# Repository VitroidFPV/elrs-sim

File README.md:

# ELRS Sim Receiver
Hardware for https://github.com/mikeneiderhauser/CRSFJoystick

> [!CAUTION]
> This hardware is untested and still awaiting ELRS target approval!
> Use/reference at own risk.

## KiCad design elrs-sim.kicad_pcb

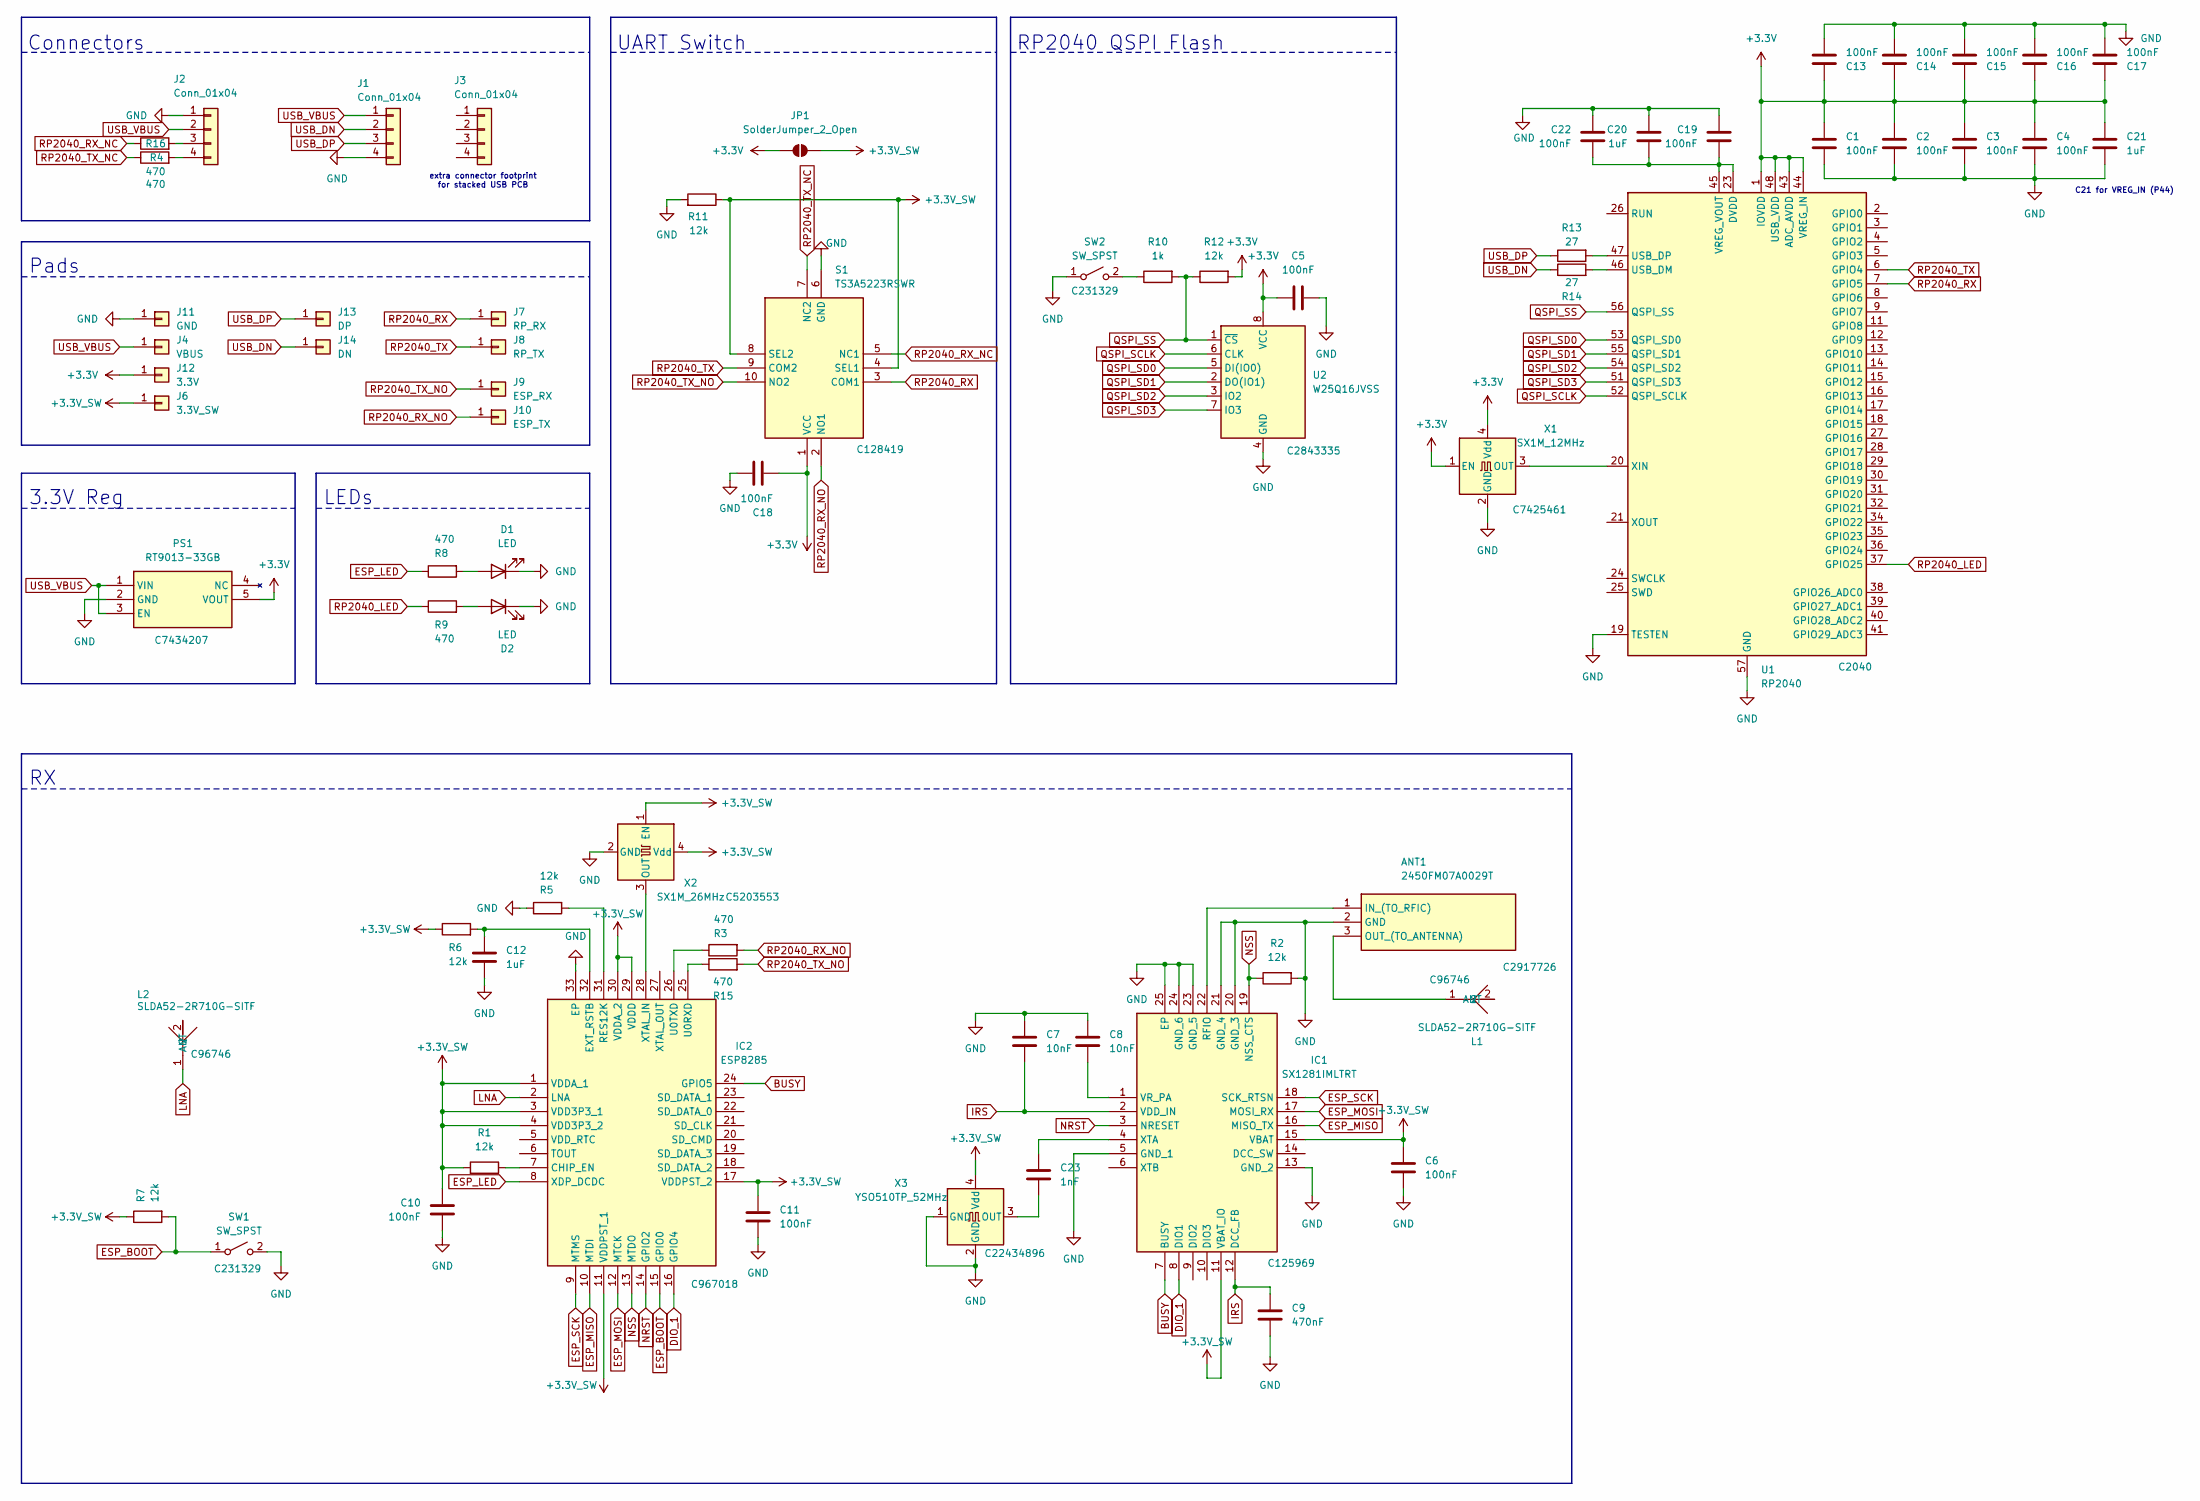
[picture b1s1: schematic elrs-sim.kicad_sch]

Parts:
ANT1: 2450FM07A0029T; Manufacturer_Part_Number 2450FM07A0029T; Mouser Part Number 609-2450FM07A0029T
C1, C2, C3, C4, C5, C6, C10, C11, C13, C14, C15, C16, C17, C18, C19, C22: 100nF; C_0402_1005Metric; LCSC C110251
C7, C8: 10nF; C_0402_1005Metric; LCSC C60133
C9: 470nF; C_0402_1005Metric; LCSC C47339
C12: 1uF; C_0402_1005Metric; LCSC C110251
C20, C21: 1uF; C_0402_1005Metric; LCSC C14445
C23: 1nF; C_0402_1005Metric; LCSC C1523
D1: LED; LED_0603_1608Metric; LCSC C84266
D2: LED; LED_0603_1608Metric; LCSC C84267
IC1: SX1281IMLTRT; QFN50P400X400X100-25N-D; Manufacturer_Part_Number SX1280IMLTRT; Mouser Part Number 947-SX1280IMLTRT
IC2: ESP8285; QFN50P500X500X90-33N-D; Manufacturer_Part_Number ESP8285; Mouser Part Number 356-ESP8285
J1: Conn_01x04; PCB_USB_connector
J2: Conn_01x04; PinHeader_1x04_P2.54mm_Vertical
J3: Conn_01x04; PCB_USB_connector_top
J4: VBUS; PAD_1.5x1.5mm_NO_HOLE
J6: 3.3V_SW; PAD_1.5x1.5mm_NO_HOLE
J7: RP_RX; PAD_1.5x1.5mm_NO_HOLE
J8: RP_TX; PAD_1.5x1.5mm_NO_HOLE
J9: ESP_RX; PAD_1.5x1.5mm_NO_HOLE
J10: ESP_TX; PAD_1.5x1.5mm_NO_HOLE
J11: GND; PAD_1.5x1.5mm_NO_HOLE
J12: 3.3V; PAD_1.5x1.5mm_NO_HOLE
J13: DP; PAD_1.5x1.5mm_NO_HOLE
J14: DN; PAD_1.5x1.5mm_NO_HOLE
JP1: SolderJumper_2_Open; SolderJumper-2_P1.3mm_Open_TrianglePad1.0x1.5mm
L1, L2: SLDA52-2R710G-SITF; ANT-SMD_L5.2-W2.1; LCSC Part C96746
PS1: RT9013-33GB; SOT-23-5; Manufacturer_Part_Number RT9013-33GB; LCSC C7434207
R1, R2, R5, R6, R7, R11, R12: 12k; R_0402_1005Metric; LCSC C22790
R3, R4, R8, R9, R15, R16: 470; R_0402_1005Metric; LCSC C25117
R10: 1k; R_0402_1005Metric; LCSC C11702
R13, R14: 27; R_0402_1005Metric; LCSC C25100
S1: TS3A5223RSWR; UQFN-10_1.3x1.8mm_P0.4mm; Manufacturer_Part_Number TS3A5223RSWR; Mouser Part Number 595-TS3A5223RSWR
SW1, SW2: SW_SPST; SW_SPST_B3U-1000P; LCSC C231329
U1: RP2040; QFN-56-1EP_7x7mm_P0.4mm_EP3.2x3.2mm; LCSC C2040
U2: W25Q16JVSS; Winbond_USON-8-1EP_3x2mm_P0.5mm_EP0.2x1.6mm; LCSC C2843335
X1: SX1M_12MHz; Crystal_SMD_SeikoEpson_FA128-4Pin_2.0x1.6mm; LCSC C7425461
X2: SX1M_26MHz; Crystal_SMD_SeikoEpson_FA128-4Pin_2.0x1.6mm; LCSC C5203553
X3: YSO510TP_52MHz; Crystal_SMD_SeikoEpson_FA128-4Pin_2.0x1.6mm; LCSC C22434896

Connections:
+3.3V: C1.1, C2.1, C3.1, C4.1, C5.1, C13.1, C14.1, C15.1, C16.1, C17.1, C18.2, C21.1, J12.1, JP1.1 (A), PS1.5 (VOUT), R12.2, S1.1 (VCC), U1.1 (IOVDD), U1.10 (IOVDD), U1.22 (IOVDD), U1.33 (IOVDD), U1.42 (IOVDD), U1.43 (ADC_AVDD), U1.44 (VREG_IN), U1.48 (USB_VDD), U1.49 (IOVDD), U2.8 (VCC), X1.1 (EN), X1.4 (Vdd)
+3.3V_SW: C6.1, C10.1, C11.1, IC1.11 (VBAT_IO), IC1.15 (VBAT), IC2.1 (VDDA_1), IC2.3 (VDD3P3_1), IC2.4 (VDD3P3_2), IC2.11 (VDDPST_1), IC2.17 (VDDPST_2), IC2.29 (VDDD), IC2.30 (VDDA_2), J6.1, JP1.2 (B), R1.2, R6.1, R7.1, R11.1, S1.4 (SEL1), S1.8 (SEL2), X2.1 (EN), X2.4 (Vdd), X3.4 (Vdd)
BUSY: IC1.7 (BUSY), IC2.24 (GPIO5)
DIO_1: IC1.8 (DIO1), IC2.16 (GPIO4)
ESP_BOOT: IC2.15 (GPIO0), R7.2, SW1.1 (A)
ESP_LED: IC2.8 (XDP_DCDC), R8.1
ESP_MISO: IC1.16 (MISO_TX), IC2.10 (MTDI)
ESP_MOSI: IC1.17 (MOSI_RX), IC2.12 (MTCK)
ESP_SCK: IC1.18 (SCK_RTSN), IC2.9 (MTMS)
GND: ANT1.2 (GND), C1.2, C2.2, C3.2, C4.2, C5.2, C6.2, C7.1, C8.1, C9.2, C10.2, C11.2, C12.2, C13.2, C14.2, C15.2, C16.2, C17.2, C18.1, C19.1, C20.1, C21.2, C22.1, D1.1 (K), D2.1 (K), IC1.5 (GND_1), IC1.13 (GND_2), IC1.20 (GND_3), IC1.21 (GND_4), IC1.23 (GND_5), IC1.24 (GND_6), IC1.25 (EP), IC2.33 (EP), J1.4, J2.1, J11.1, PS1.2 (GND), R2.2, R5.1, R11.2, S1.6 (GND), SW1.2 (B), SW2.1 (A), U1.19 (TESTEN), U1.57 (GND), U2.4 (GND), X1.2 (GND), X2.2 (GND), X3.1 (GND), X3.2 (GND)
IRS: C7.2, C9.1, IC1.2 (VDD_IN), IC1.12 (DCC_FB)
LNA: IC2.2 (LNA), L2.1 (ANT)
NRST: IC1.3 (NRESET), IC2.14 (GPIO2)
NSS: IC1.19 (NSS_CTS), IC2.13 (MTDO), R2.1
unnamed: ANT1.1 (IN_(TO_RFIC)), IC1.22 (RFIO)
unnamed: ANT1.3 (OUT_(TO_ANTENNA)), L1.1 (ANT)
unnamed: D1.2 (A), R8.2
unnamed: D2.2 (A), R9.2
unnamed: C8.2, IC1.1 (VR_PA)
unnamed: C23.1, IC1.4 (XTA)
unnamed: IC2.7 (CHIP_EN), R1.1
unnamed: C12.1, IC2.32 (EXT_RSTB), R6.2
unnamed: IC2.31 (RES12K), R5.2
unnamed: IC2.25 (U0RXD), R15.1
unnamed: IC2.26 (U0TXD), R3.1
unnamed: IC2.28 (XTAL_IN), X2.3 (OUT)
unnamed: J2.3, R16.2
unnamed: J2.4, R4.2
unnamed: R10.1, SW2.2 (B)
unnamed: R14.2, U1.46 (USB_DM)
unnamed: R13.2, U1.47 (USB_DP)
unnamed: C19.2, C20.2, C22.2, U1.23 (DVDD), U1.45 (VREG_VOUT), U1.50 (DVDD)
unnamed: U1.20 (XIN), X1.3 (OUT)
unnamed: C23.2, X3.3 (OUT)
QSPI_SCLK: U1.52 (QSPI_SCLK), U2.6 (CLK)
QSPI_SD0: U1.53 (QSPI_SD0), U2.5 (DI(IO0))
QSPI_SD1: U1.55 (QSPI_SD1), U2.2 (DO(IO1))
QSPI_SD2: U1.54 (QSPI_SD2), U2.3 (IO2)
QSPI_SD3: U1.51 (QSPI_SD3), U2.7 (IO3)
QSPI_SS: R10.2, R12.1, U1.56 (QSPI_SS), U2.1 (~CS)
RP2040_LED: R9.1, U1.37 (GPIO25)
RP2040_RX: J7.1, S1.3 (COM1), U1.7 (GPIO5)
RP2040_RX_NC: R16.1, S1.5 (NC1)
RP2040_RX_NO: J10.1, R3.2, S1.2 (NO1)
RP2040_TX: J8.1, S1.9 (COM2), U1.6 (GPIO4)
RP2040_TX_NC: R4.1, S1.7 (NC2)
RP2040_TX_NO: J9.1, R15.2, S1.10 (NO2)
USB_DN: J1.2, J14.1, R14.1
USB_DP: J1.3, J13.1, R13.1
USB_VBUS: J1.1, J2.2, J4.1, PS1.1 (VIN), PS1.3 (EN)

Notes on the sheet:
Connectors
C21 for VREG_IN (P44)
3.3V Reg
extra connector footprint for stacked USB PCB
UART Switch
RP2040 QSPI Flash
Pads
LEDs

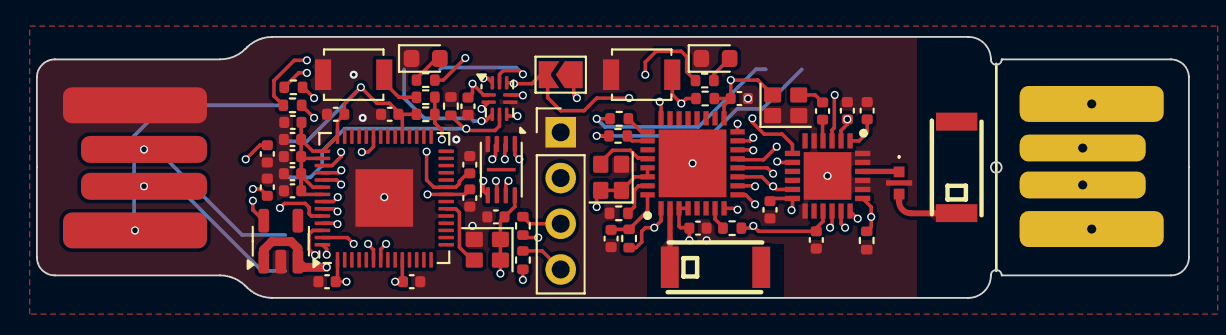
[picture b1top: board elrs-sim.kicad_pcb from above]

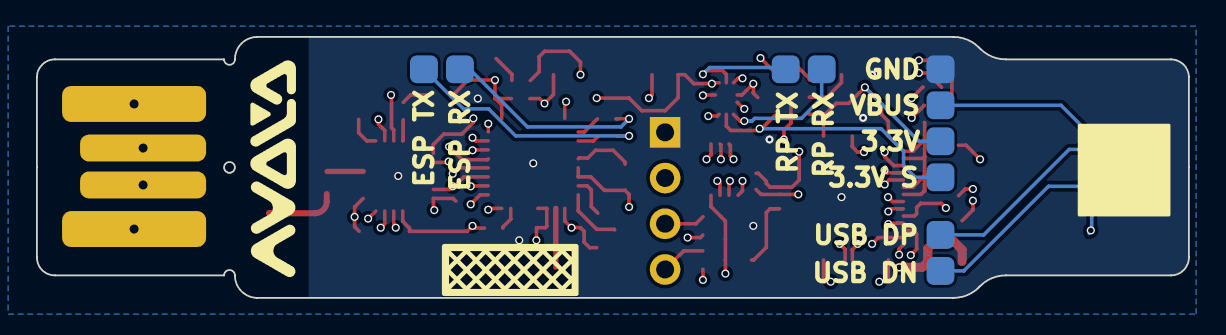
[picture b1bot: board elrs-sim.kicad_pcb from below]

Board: 4 copper layers, 64.0 x 14.5 mm, 69 parts (10 on the bottom side), 50 nets.

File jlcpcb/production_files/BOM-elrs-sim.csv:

Comment,Designator,Footprint,LCSC
100nF,"C1,C10,C11,C12,C13,C14,C15,C16,C17,C18,C19,C2,C22,C3,C4,C5,C6",C_0402_1005Metric,C110251
1k,R10,R_0402_1005Metric,C11702
SX1280IMLTRT,IC1,QFN50P400X400X100-25N-D,C125969
TS3A5223RSWR,S1,UQFN-10_1.3x1.8mm_P0.4mm,C128419
1uF,"C20,C21",C_0402_1005Metric,C14445
RP2040,U1,QFN-56-1EP_7x7mm_P0.4mm_EP3.2x3.2mm,C2040
YSO510TP_52MHz,X3,Crystal_SMD_SeikoEpson_FA128-4Pin_2.0x1.6mm,C22434896
12k,"R1,R11,R12,R2,R5,R6,R7",R_0402_1005Metric,C22790
SW_SPST,"SW1,SW2",SW_SPST_B3U-1000P,C231329
27,"R13,R14",R_0402_1005Metric,C25100
470,"R15,R16,R3,R4,R8,R9",R_0402_1005Metric,C25117
W25Q16JVSS,U2,Winbond_USON-8-1EP_3x2mm_P0.5mm_EP0.2x1.6mm,C2843335
2450FM07A0029T,ANT1,2450FM07A0029T,C2917726
470nF,C9,C_0402_1005Metric,C47339
SX1M_26MHz,X2,Crystal_SMD_SeikoEpson_FA128-4Pin_2.0x1.6mm,C5203553
1nF,"C23,C7,C8",C_0402_1005Metric,C60133
SX1M_12MHz,X1,Crystal_SMD_SeikoEpson_FA128-4Pin_2.0x1.6mm,C7425461
RT9013-33GB,PS1,SOT-23-5,C7434207
LED,D1,LED_0603_1608Metric,C84266
LED,D2,LED_0603_1608Metric,C84267
ESP8285,IC2,QFN50P500X500X90-33N-D,C967018
SLDA52-2R710G-SITF,"L1,L2",ANT-SMD_L5.2-W2.1,C96746

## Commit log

2024-09-10 Update: BOM and prod files
2024-09-10 Update: Plot updated SCH
2024-09-10 Update: JLCPCB requirements
2024-09-10 Update: Add JLCPCB tracking QR rect
2024-10-07 Update main board
2024-10-07 Update prod files
2024-10-07 Experimental panels
2024-10-07 Update: larger tolerances, better board shape
2024-10-07 Update: Smooth out antenna traces
2024-10-07 Prod: New shape prod files
2024-10-09 Update: Use SX1281, check BOM, hopefully final 0.0.1 prod files
2024-10-14 Chore: JLCPCB took it as two designs, hopefully this passes as one
